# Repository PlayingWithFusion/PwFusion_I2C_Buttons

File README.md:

# PwFusion_I2C_Buttons

Are you looking for a way to take your project to the next level? Playing with Fusion's I2C Buttons board is the way to go! This device greatly simplifies connectivity to a microcontroller through the QWIIC system. The typical 6 wires required to use 5 push buttons with a microcontroller can be reduced to one QWIIC cable. You can even chain multiple QWIIC devices together for maximum wiring efficiency! If that isn't enough, Playing with Fusion provides Arduino libraries to make writing code for these boards as easy as possible! Weather you are a beginner looking for a simple introduction to the world of hobbyist electronics or an advanced user looking for a rapid prototyping tool, Playing with Fusion's I2C Buttons board is right for you!

## I2C Addresses

| ADR 0   |   ADR 1   |   Address |
| --- | --- | --- |
| uncut   |   uncut   |   0x09 |
| cut     |   uncut   |   0x10 |
| uncut   |   cut     |   0x11 |
| cut     |   cut     |   0x12 |

The Playing with Fusion I2C buttons board comes with 4 available I2C addresses, which can be easily selected by cutting the jumpers on the printed circuit board. This allows for 4 button boards to be used on the same QWIIC chain. If you would like more than 4, see docs/Programming Instructions and flash a modified firmware with additional I2C address options.

## Example Projects
RC Transmitter: https://github.com/PlayingWithFusion/RC_Transmitter

## Related

| Page | Link |
| --- | --- |
| PwFusion_I2C_Buttons_Arduino_Library:  | https://github.com/PlayingWithFusion/PwFusion_I2C_Buttons_Arduino_Library |
| PwFusion_Data_Transfer:           |      https://github.com/PlayingWithFusion/PwFusion_Data_Transfer |
| IFB-40001 PwFusion_I2C_Encoder:   |  https://github.com/PlayingWithFusion/PwFusion_I2C_Encoder |
| IFB-40002 PwFusion_I2C_Joystick:  |  https://github.com/PlayingWithFusion/PwFusion_I2C_Joystick |
| IFB-40003 PwFusion_I2C_Switch:    |  https://github.com/PlayingWithFusion/PwFusion_I2C_Switch |
| IFB-40004 PwFusion_I2C_Buttons:   |  https://github.com/PlayingWithFusion/PwFusion_I2C_Buttons |

Visit https://www.playingwithfusion.com/ for more information.

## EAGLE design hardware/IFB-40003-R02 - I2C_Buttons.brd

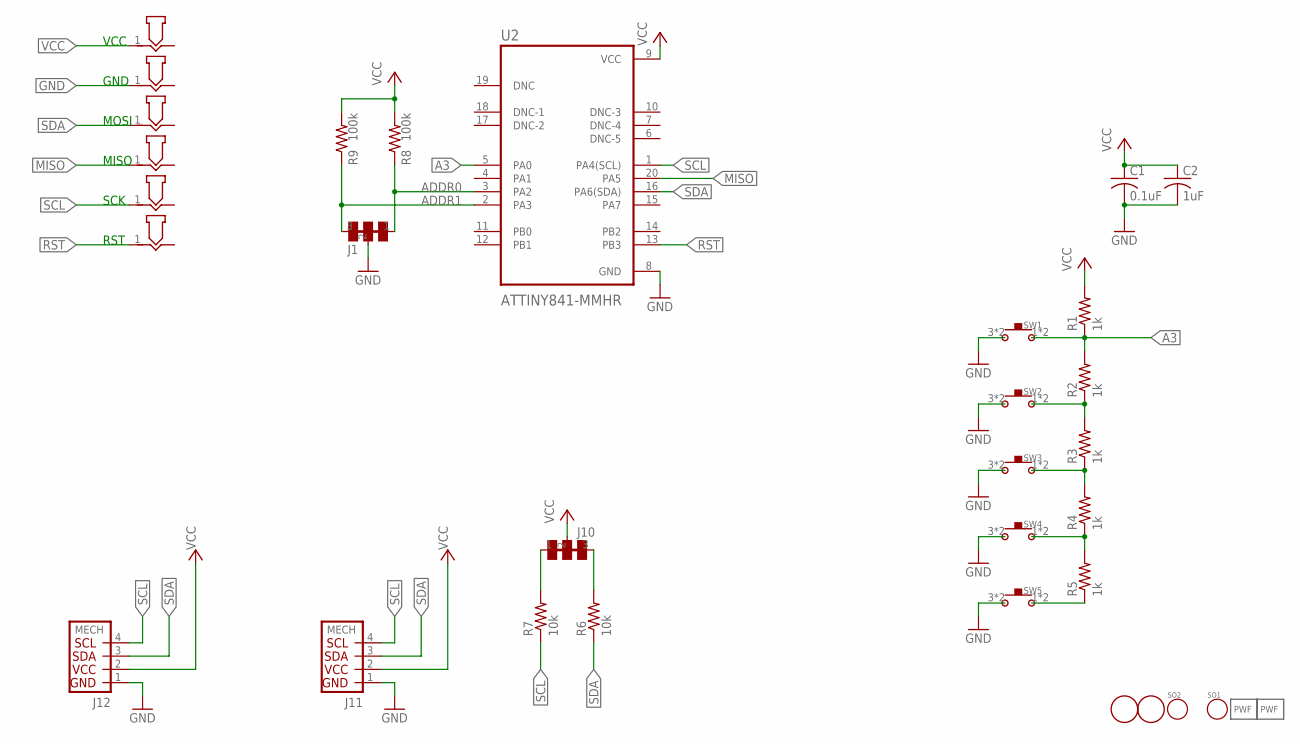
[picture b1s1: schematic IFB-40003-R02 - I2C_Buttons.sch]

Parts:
C1: 0.1uF; C0603K
C2: 1uF; C0603K
J1, J10: CUT_JUMPER_2X; SMT_2X_CUTTABLE_JUMPER
J4, J5, J6, J7, J8, J9: POGO_PAD; P50_POGO_BOARD_CONTACT_12MIL
J11, J12: QWIICSIDE; SM04B-SRSS-TB
LOGO1: PWF_LOGOPWF-6MM-SS; LOGO_6MM_STEIN
LOGO2: PWF_LOGOPWF-12MM-SS; LOGO_12MM_STEIN
R1, R2, R3, R4, R5: 1k; R0603
R6, R7: 10k; R0603
R8, R9: 100k; R0603
SO1, SO2: STAND_OFFNO4_TIGHT; STANDOFF_NO4_TIGHT
SW1, SW2, SW3, SW4, SW5: PTS6455MM; PTS645_5MM
U2: ATTINY841-MMHR; QFN45P300X300X85-21N
U$2, U$3: FIDUCIAL; FIDUCIAL_1MM

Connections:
A3: R1.1, R2.2, SW1.1, SW1.2 (1), U2.5 (PA0)
ADDR0: J1.1, R8.1, U2.3 (PA2)
ADDR1: J1.3, R9.1, U2.2 (PA3)
GND: C1.2, C2.2, J1.2, J5.1, J11.1, J12.1, SW1.3, SW1.4 (3), SW2.3, SW2.4 (3), SW3.3, SW3.4 (3), SW4.3, SW4.4 (3), SW5.3, SW5.4 (3), U2.8 (GND)
MISO: J7.1, U2.20 (PA5)
unnamed: R2.1, R3.2, SW2.1, SW2.2 (1)
unnamed: R3.1, R4.2, SW3.1, SW3.2 (1)
unnamed: R4.1, R5.2, SW4.1, SW4.2 (1)
unnamed: R5.1, SW5.1, SW5.2 (1)
unnamed: J10.1, R7.2
unnamed: J10.3, R6.2
RST: J9.1, U2.13 (PB3)
SCL: J8.1, J11.4, J12.4, R7.1, U2.1 (PA4(SCL))
SDA: J6.1, J11.3, J12.3, R6.1, U2.16 (PA6(SDA))
VCC: C1.1, C2.1, J4.1, J10.2, J11.2, J12.2, R1.2, R8.2, R9.2, U2.9 (VCC)

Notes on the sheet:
VCC
GND
MOSI
MISO
SCK
RST

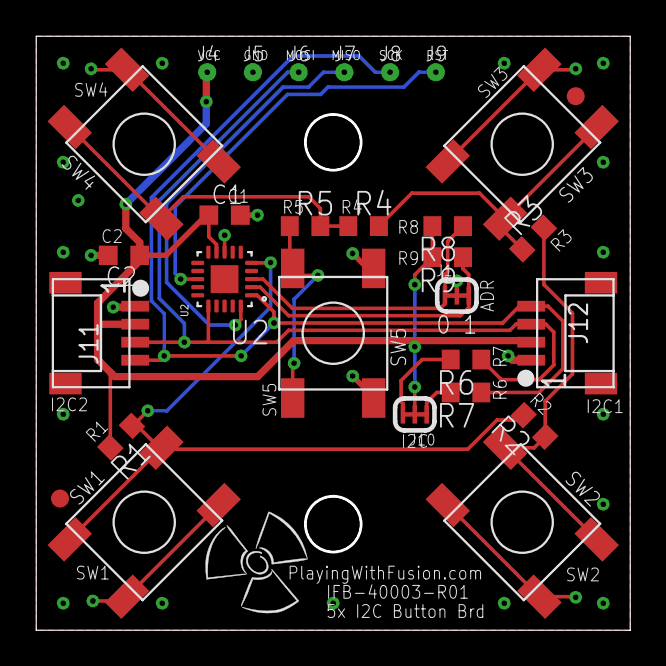
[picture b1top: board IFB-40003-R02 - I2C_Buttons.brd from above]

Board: 2 copper layers, 32.9 x 32.9 mm, 33 parts (1 on the bottom side), 15 nets.

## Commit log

2023-10-01 Added firmware and readme
2023-10-08 hardware and links
2023-10-29 added programming instructions
2023-12-02 updated addresses
2023-12-02 updated hardware files
2024-07-05 updated firmware flash instructions
